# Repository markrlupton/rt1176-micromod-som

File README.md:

# RT1176 MicroMod SOM

An NXP i.MX RT1176 (Cortex-M7 1 GHz + Cortex-M4 400 MHz) on a MicroMod processor card (M.2 2222 Key E). It uses the SparkFun MicroMod Teensy pinout, so it drops into the RaceLink intercom carrier in place of the MicroMod Teensy.

- **Status:** stage 4 done: fab files in `fab/`, ordering notes in `docs/FAB_NOTES.md`, hand-build guide in `docs/HAND_BUILD.md`.
- **Schematic:** [docs/schematic.pdf](docs/schematic.pdf). Generated by `tools/schgen.py`; regenerate rather than editing in KiCad.
- **Design decisions and open items:** [docs/DESIGN.md](docs/DESIGN.md)
- **Pin map:** [docs/PINOUT.md](docs/PINOUT.md). Generated from `tools/pinmap.py`; don't edit by hand.
- **Floorplan:** [docs/floorplan_v1.png](docs/floorplan_v1.png)

## Tools

KiCad 7 + Python, the same toolchain as the intercom carrier.

| Script | Does |
|---|---|
| `tools/pinmap.py` | Single source of truth: MicroMod pin -> RT1176 pad and function |
| `tools/verify.py` | Checks the pin map against NXP's pin-mux data (Zephyr hal_nxp) and the RT1176 ball map: function exists on the pad, no pad used twice, every Teensy pin covered |
| `tools/mktable.py` | Regenerates docs/PINOUT.md |
| `tools/optimize_pins.py` | Picks RT1176 pads for each MicroMod signal to keep ball-to-finger routes short |
| `tools/floorplan.py` | Regenerates the floorplan drawing |
| `tools/libgen.py` | Builds `lib/`: RT1176 symbol (6 units, from the ball map), MicroMod card symbol and edge-finger footprint |
| `tools/schgen.py` | Builds the KiCad 7 schematic (root + 4 sheets) from one parts/nets table |
| `tools/schcheck.py` | Exports the netlist with kicad-cli and checks it against the design table, the pin map and NXP's rail rules |

Regenerate everything: `python3 tools/libgen.py && python3 tools/schgen.py && python3 tools/schcheck.py`

## Fabrication (stage 4)

`python3 tools/fab.py` writes `fab/`: Gerbers and drill (`fab/rt1176-micromod-som-gerbers.zip`), JLC BOM and
placement files, assembly drawings, a hand-build stencil, and the DRC report. Order settings: `docs/FAB_NOTES.md`.
Hand assembly: `docs/HAND_BUILD.md`.

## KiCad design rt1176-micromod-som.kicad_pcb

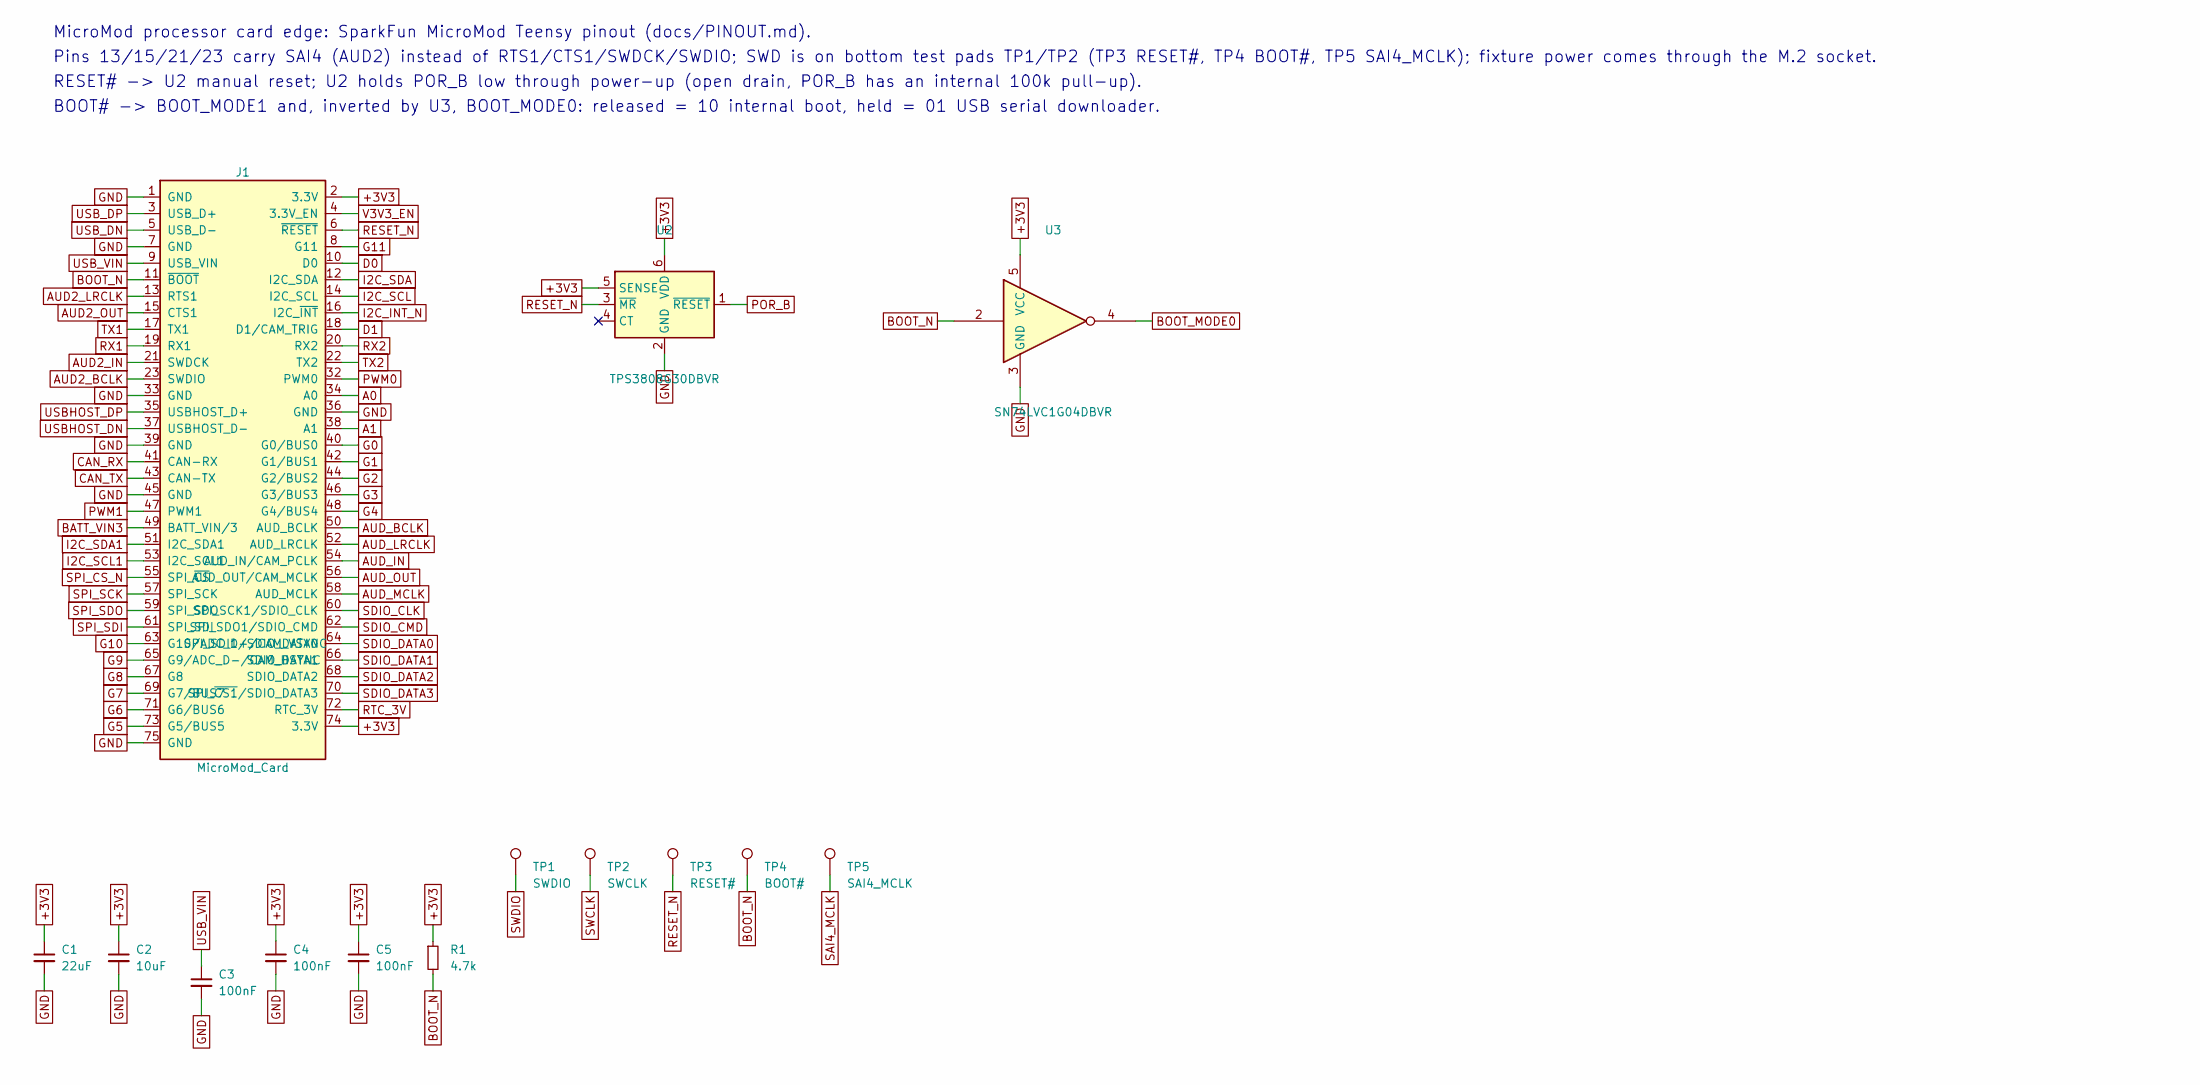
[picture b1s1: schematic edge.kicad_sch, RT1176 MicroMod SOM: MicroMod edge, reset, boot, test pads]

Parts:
C1: 22uF; C_0805_2012Metric
C2: 10uF; C_0805_2012Metric
C3, C4, C5: 100nF; C_0603_1608Metric
J1: MicroMod_Card; MicroMod_Card_Edge
R1: 4.7k; R_0603_1608Metric
TP1: SWDIO; TestPoint_Pad_D1.0mm
TP2: SWCLK; TestPoint_Pad_D1.0mm
TP3: RESET#; TestPoint_Pad_D1.0mm
TP4: BOOT#; TestPoint_Pad_D1.0mm
TP5: SAI4_MCLK; TestPoint_Pad_D1.0mm
U2: TPS3808G30DBVR; SOT-23-6; MPN TPS3808G30DBVR; LCSC C189211
U3: SN74LVC1G04DBVR; SOT-23-5; MPN SN74LVC1G04DBVR; LCSC C7827

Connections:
+3V3: C1.1, C2.1, C4.1, C5.1, J1.2 (3.3V), J1.74 (3.3V), R1.1, U2.5 (SENSE), U2.6 (VDD), U3.5 (VCC); also elsewhere on the board
A0: J1.34 (A0); also elsewhere on the board
A1: J1.38 (A1); also elsewhere on the board
AUD2_BCLK: J1.23 (SWDIO); also elsewhere on the board
AUD2_IN: J1.21 (SWDCK); also elsewhere on the board
AUD2_LRCLK: J1.13 (RTS1); also elsewhere on the board
AUD2_OUT: J1.15 (CTS1); also elsewhere on the board
AUD_BCLK: J1.50 (AUD_BCLK); also elsewhere on the board
AUD_IN: J1.54 (AUD_IN/CAM_PCLK); also elsewhere on the board
AUD_LRCLK: J1.52 (AUD_LRCLK); also elsewhere on the board
AUD_MCLK: J1.58 (AUD_MCLK); also elsewhere on the board
AUD_OUT: J1.56 (AUD_OUT/CAM_MCLK); also elsewhere on the board
BATT_VIN3: J1.49 (BATT_VIN/3); also elsewhere on the board
BOOT_MODE0: U3.4; also elsewhere on the board
BOOT_N: J1.11 (~BOOT), R1.2, TP4.1, U3.2; also elsewhere on the board
CAN_RX: J1.41 (CAN-RX); also elsewhere on the board
CAN_TX: J1.43 (CAN-TX); also elsewhere on the board
D0: J1.10 (D0); also elsewhere on the board
D1: J1.18 (D1/CAM_TRIG); also elsewhere on the board
G0: J1.40 (G0/BUS0); also elsewhere on the board
G1: J1.42 (G1/BUS1); also elsewhere on the board
G2: J1.44 (G2/BUS2); also elsewhere on the board
G3: J1.46 (G3/BUS3); also elsewhere on the board
G4: J1.48 (G4/BUS4); also elsewhere on the board
G5: J1.73 (G5/BUS5); also elsewhere on the board
G6: J1.71 (G6/BUS6); also elsewhere on the board
G7: J1.69 (G7/BUS7); also elsewhere on the board
G8: J1.67 (G8); also elsewhere on the board
G9: J1.65 (G9/ADC_D-/CAM_HSYNC); also elsewhere on the board
G10: J1.63 (G10/ADC_D+/CAM_VSYNC); also elsewhere on the board
G11: J1.8 (G11); also elsewhere on the board
GND: C1.2, C2.2, C3.2, C4.2, C5.2, J1.1 (GND), J1.7 (GND), J1.33 (GND), J1.36 (GND), J1.39 (GND), J1.45 (GND), J1.75 (GND), U2.2 (GND), U3.3 (GND); also elsewhere on the board
I2C_INT_N: J1.16 (I2C_~INT); also elsewhere on the board
I2C_SCL: J1.14 (I2C_SCL); also elsewhere on the board
I2C_SCL1: J1.53 (I2C_SCL1); also elsewhere on the board
I2C_SDA: J1.12 (I2C_SDA); also elsewhere on the board
I2C_SDA1: J1.51 (I2C_SDA1); also elsewhere on the board
POR_B: U2.1 (~RESET); also elsewhere on the board
PWM0: J1.32 (PWM0); also elsewhere on the board
PWM1: J1.47 (PWM1); also elsewhere on the board
RESET_N: J1.6 (~RESET), TP3.1, U2.3 (~MR)
RTC_3V: J1.72 (RTC_3V); also elsewhere on the board
RX1: J1.19 (RX1); also elsewhere on the board
RX2: J1.20 (RX2); also elsewhere on the board
SAI4_MCLK: TP5.1; also elsewhere on the board
SDIO_CLK: J1.60 (SPI_SCK1/SDIO_CLK); also elsewhere on the board
SDIO_CMD: J1.62 (SPI_SDO1/SDIO_CMD); also elsewhere on the board
SDIO_DATA0: J1.64 (SPI_SDI1/SDIO_DATA0); also elsewhere on the board
SDIO_DATA1: J1.66 (SDIO_DATA1); also elsewhere on the board
SDIO_DATA2: J1.68 (SDIO_DATA2); also elsewhere on the board
SDIO_DATA3: J1.70 (SPI_~CS1/SDIO_DATA3); also elsewhere on the board
SPI_CS_N: J1.55 (SPI_~CS); also elsewhere on the board
SPI_SCK: J1.57 (SPI_SCK); also elsewhere on the board
SPI_SDI: J1.61 (SPI_SDI); also elsewhere on the board
SPI_SDO: J1.59 (SPI_SDO); also elsewhere on the board
SWCLK: TP2.1; also elsewhere on the board
SWDIO: TP1.1; also elsewhere on the board
TX1: J1.17 (TX1); also elsewhere on the board
TX2: J1.22 (TX2); also elsewhere on the board
USBHOST_DN: J1.37 (USBHOST_D-); also elsewhere on the board
USBHOST_DP: J1.35 (USBHOST_D+); also elsewhere on the board
USB_DN: J1.5 (USB_D-); also elsewhere on the board
USB_DP: J1.3 (USB_D+); also elsewhere on the board
USB_VIN: C3.1, J1.9 (USB_VIN); also elsewhere on the board
V3V3_EN: J1.4 (3.3V_EN); also elsewhere on the board

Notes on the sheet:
MicroMod processor card edge: SparkFun MicroMod Teensy pinout (docs/PINOUT.md).
Pins 13/15/21/23 carry SAI4 (AUD2) instead of RTS1/CTS1/SWDCK/SWDIO; SWD is on bottom test pads TP1/TP2 (TP3 RESET#, TP4 BOOT#, TP5 SAI4_MCLK); fixture power comes through the M.2 socket.
RESET# -> U2 manual reset; U2 holds POR_B low through power-up (open drain, POR_B has an internal 100k pull-up).
BOOT# -> BOOT_MODE1 and, inverted by U3, BOOT_MODE0: released = 10 internal boot, held = 01 USB serial downloader.

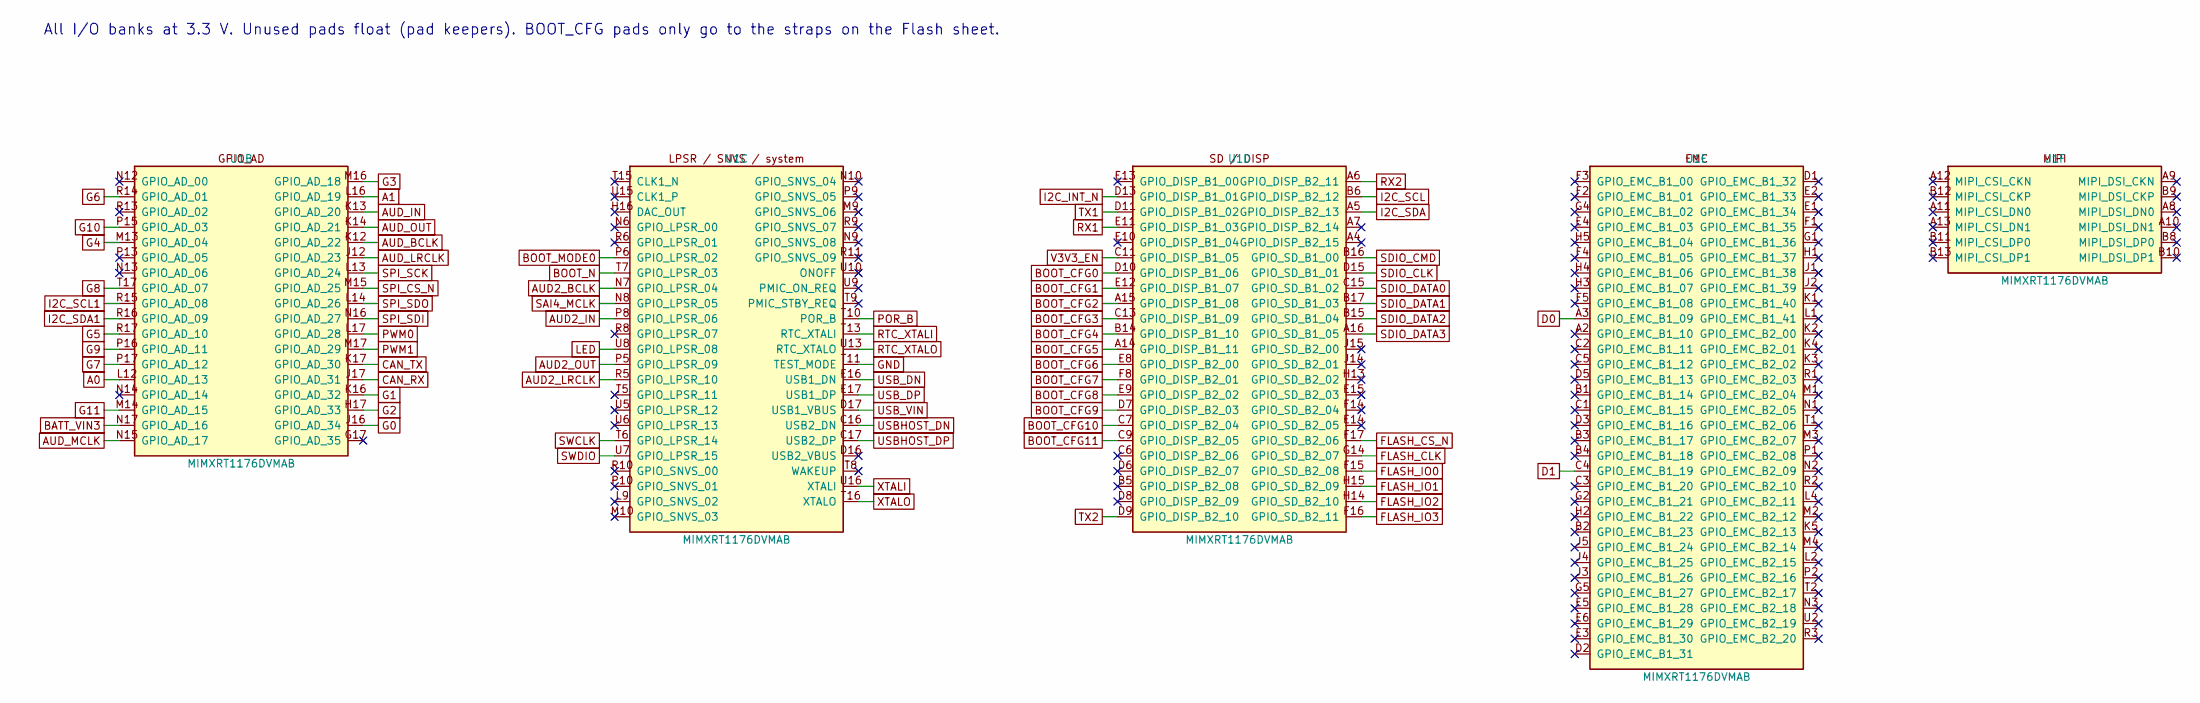
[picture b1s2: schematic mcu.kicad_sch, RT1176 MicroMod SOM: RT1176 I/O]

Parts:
U1: MIMXRT1176DVMAB; MAPBGA_14x14mm_Layout17x17_P0.8mm; MPN MIMXRT1176DVMAB

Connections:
A0: U1.L12 (GPIO_AD_13); also elsewhere on the board
A1: U1.L16 (GPIO_AD_19); also elsewhere on the board
AUD2_BCLK: U1.N7 (GPIO_LPSR_04); also elsewhere on the board
AUD2_IN: U1.P8 (GPIO_LPSR_06); also elsewhere on the board
AUD2_LRCLK: U1.R5 (GPIO_LPSR_10); also elsewhere on the board
AUD2_OUT: U1.P5 (GPIO_LPSR_09); also elsewhere on the board
AUD_BCLK: U1.K12 (GPIO_AD_22); also elsewhere on the board
AUD_IN: U1.K13 (GPIO_AD_20); also elsewhere on the board
AUD_LRCLK: U1.J12 (GPIO_AD_23); also elsewhere on the board
AUD_MCLK: U1.N15 (GPIO_AD_17); also elsewhere on the board
AUD_OUT: U1.K14 (GPIO_AD_21); also elsewhere on the board
BATT_VIN3: U1.N17 (GPIO_AD_16); also elsewhere on the board
BOOT_CFG0: U1.D10 (GPIO_DISP_B1_06); also elsewhere on the board
BOOT_CFG1: U1.E12 (GPIO_DISP_B1_07); also elsewhere on the board
BOOT_CFG2: U1.A15 (GPIO_DISP_B1_08); also elsewhere on the board
BOOT_CFG3: U1.C13 (GPIO_DISP_B1_09); also elsewhere on the board
BOOT_CFG4: U1.B14 (GPIO_DISP_B1_10); also elsewhere on the board
BOOT_CFG5: U1.A14 (GPIO_DISP_B1_11); also elsewhere on the board
BOOT_CFG6: U1.E8 (GPIO_DISP_B2_00); also elsewhere on the board
BOOT_CFG7: U1.F8 (GPIO_DISP_B2_01); also elsewhere on the board
BOOT_CFG8: U1.E9 (GPIO_DISP_B2_02); also elsewhere on the board
BOOT_CFG9: U1.D7 (GPIO_DISP_B2_03); also elsewhere on the board
BOOT_CFG10: U1.C7 (GPIO_DISP_B2_04); also elsewhere on the board
BOOT_CFG11: U1.C9 (GPIO_DISP_B2_05); also elsewhere on the board
BOOT_MODE0: U1.P6 (GPIO_LPSR_02); also elsewhere on the board
BOOT_N: U1.T7 (GPIO_LPSR_03); also elsewhere on the board
CAN_RX: U1.J17 (GPIO_AD_31); also elsewhere on the board
CAN_TX: U1.K17 (GPIO_AD_30); also elsewhere on the board
D0: U1.A3 (GPIO_EMC_B1_09); also elsewhere on the board
D1: U1.C4 (GPIO_EMC_B1_19); also elsewhere on the board
FLASH_CLK: U1.G14 (GPIO_SD_B2_07); also elsewhere on the board
FLASH_CS_N: U1.F17 (GPIO_SD_B2_06); also elsewhere on the board
FLASH_IO0: U1.F15 (GPIO_SD_B2_08); also elsewhere on the board
FLASH_IO1: U1.H15 (GPIO_SD_B2_09); also elsewhere on the board
FLASH_IO2: U1.H14 (GPIO_SD_B2_10); also elsewhere on the board
FLASH_IO3: U1.F16 (GPIO_SD_B2_11); also elsewhere on the board
G0: U1.J16 (GPIO_AD_34); also elsewhere on the board
G1: U1.K16 (GPIO_AD_32); also elsewhere on the board
G2: U1.H17 (GPIO_AD_33); also elsewhere on the board
G3: U1.M16 (GPIO_AD_18); also elsewhere on the board
G4: U1.M13 (GPIO_AD_04); also elsewhere on the board
G5: U1.R17 (GPIO_AD_10); also elsewhere on the board
G6: U1.R14 (GPIO_AD_01); also elsewhere on the board
G7: U1.P17 (GPIO_AD_12); also elsewhere on the board
G8: U1.T17 (GPIO_AD_07); also elsewhere on the board
G9: U1.P16 (GPIO_AD_11); also elsewhere on the board
G10: U1.P15 (GPIO_AD_03); also elsewhere on the board
G11: U1.M14 (GPIO_AD_15); also elsewhere on the board
GND: U1.T11 (TEST_MODE); also elsewhere on the board
I2C_INT_N: U1.D13 (GPIO_DISP_B1_01); also elsewhere on the board
I2C_SCL: U1.B6 (GPIO_DISP_B2_12); also elsewhere on the board
I2C_SCL1: U1.R15 (GPIO_AD_08); also elsewhere on the board
I2C_SDA: U1.A5 (GPIO_DISP_B2_13); also elsewhere on the board
I2C_SDA1: U1.R16 (GPIO_AD_09); also elsewhere on the board
LED: U1.U8 (GPIO_LPSR_08); also elsewhere on the board
POR_B: U1.T10 (POR_B); also elsewhere on the board
PWM0: U1.L17 (GPIO_AD_28); also elsewhere on the board
PWM1: U1.M17 (GPIO_AD_29); also elsewhere on the board
RTC_XTALI: U1.T13 (RTC_XTALI); also elsewhere on the board
RTC_XTALO: U1.U13 (RTC_XTALO); also elsewhere on the board
RX1: U1.E11 (GPIO_DISP_B1_03); also elsewhere on the board
RX2: U1.A6 (GPIO_DISP_B2_11); also elsewhere on the board
SAI4_MCLK: U1.N8 (GPIO_LPSR_05); also elsewhere on the board
SDIO_CLK: U1.D15 (GPIO_SD_B1_01); also elsewhere on the board
SDIO_CMD: U1.B16 (GPIO_SD_B1_00); also elsewhere on the board
SDIO_DATA0: U1.C15 (GPIO_SD_B1_02); also elsewhere on the board
SDIO_DATA1: U1.B17 (GPIO_SD_B1_03); also elsewhere on the board
SDIO_DATA2: U1.B15 (GPIO_SD_B1_04); also elsewhere on the board
SDIO_DATA3: U1.A16 (GPIO_SD_B1_05); also elsewhere on the board
SPI_CS_N: U1.M15 (GPIO_AD_25); also elsewhere on the board
SPI_SCK: U1.L13 (GPIO_AD_24); also elsewhere on the board
SPI_SDI: U1.N16 (GPIO_AD_27); also elsewhere on the board
SPI_SDO: U1.L14 (GPIO_AD_26); also elsewhere on the board
SWCLK: U1.T6 (GPIO_LPSR_14); also elsewhere on the board
SWDIO: U1.U7 (GPIO_LPSR_15); also elsewhere on the board
TX1: U1.D11 (GPIO_DISP_B1_02); also elsewhere on the board
TX2: U1.D9 (GPIO_DISP_B2_10); also elsewhere on the board
USBHOST_DN: U1.C16 (USB2_DN); also elsewhere on the board
USBHOST_DP: U1.C17 (USB2_DP); also elsewhere on the board
USB_DN: U1.E16 (USB1_DN); also elsewhere on the board
USB_DP: U1.E17 (USB1_DP); also elsewhere on the board
USB_VIN: U1.D17 (USB1_VBUS); also elsewhere on the board
V3V3_EN: U1.C11 (GPIO_DISP_B1_05); also elsewhere on the board
XTALI: U1.U16 (XTALI); also elsewhere on the board
XTALO: U1.T16 (XTALO); also elsewhere on the board

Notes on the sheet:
All I/O banks at 3.3 V. Unused pads float (pad keepers). BOOT_CFG pads only go to the straps on the Flash sheet.

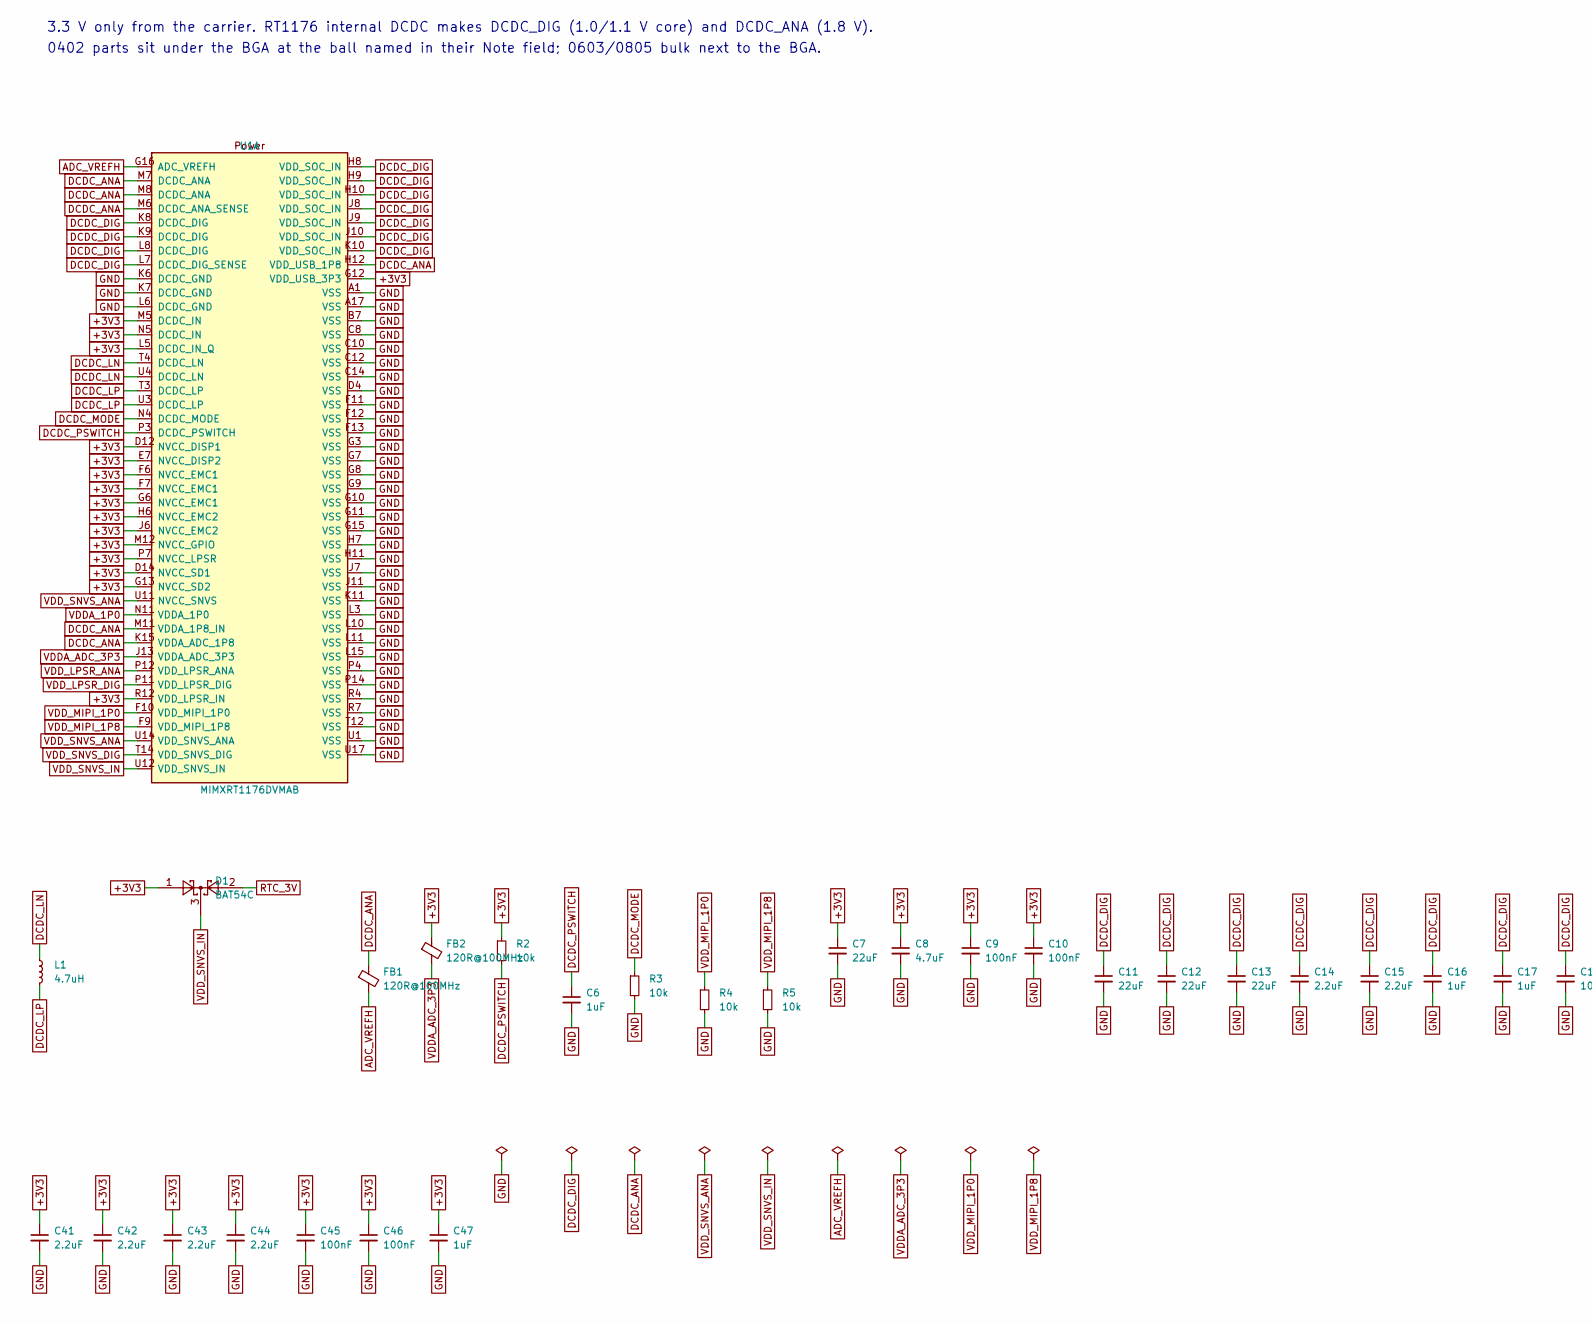
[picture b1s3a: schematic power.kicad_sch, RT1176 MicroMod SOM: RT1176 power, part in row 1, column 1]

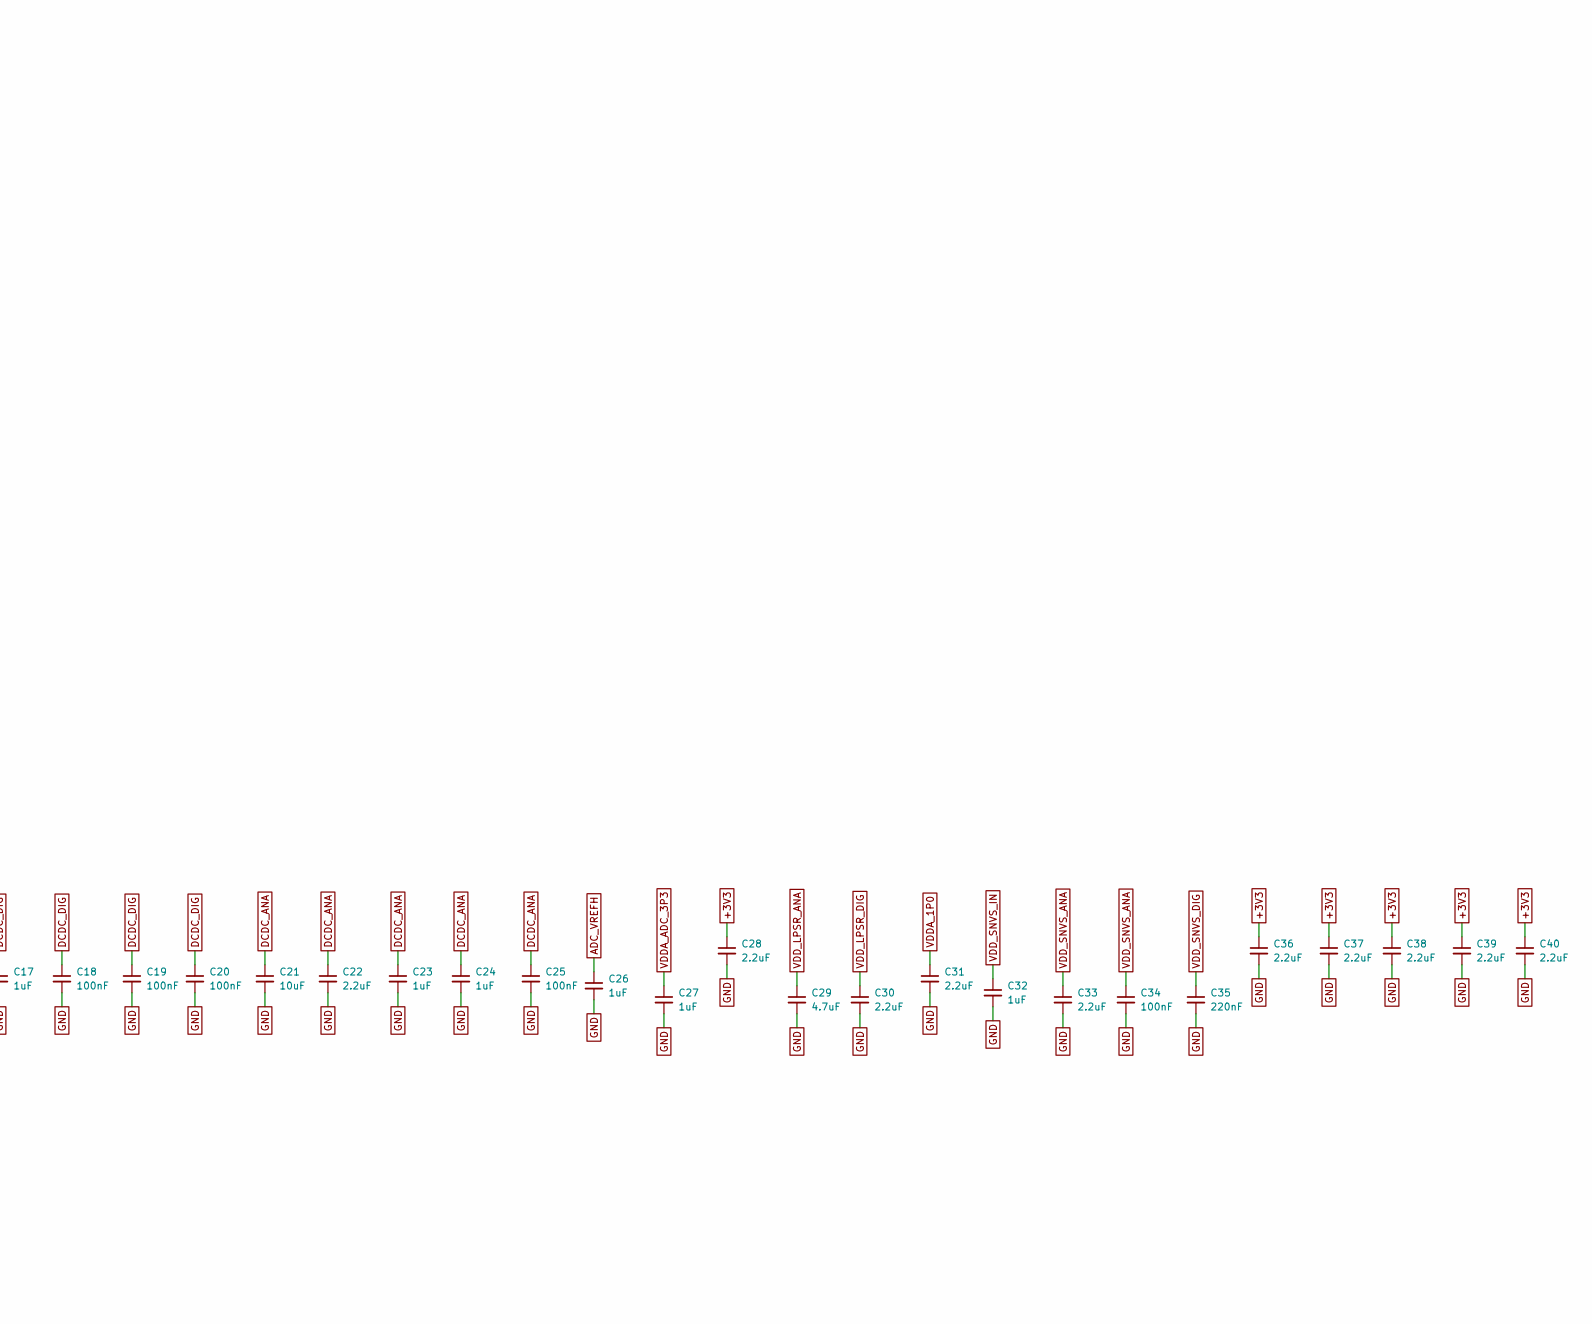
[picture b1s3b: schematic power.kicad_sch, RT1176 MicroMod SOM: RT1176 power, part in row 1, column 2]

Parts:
C6, C16, C17, C23, C24, C26, C27, C32, C47: 1uF; C_0402_1005Metric
C7, C11, C12, C13: 22uF; C_0805_2012Metric
C8: 4.7uF; C_0603_1608Metric
C9, C10, C18, C19, C20, C25, C34, C45, C46: 100nF; C_0402_1005Metric
C14, C15, C22, C28, C30, C31, C33, C36, C37, C38, C39, C40, C41, C42, C43, C44: 2.2uF; C_0402_1005Metric
C21: 10uF; C_0603_1608Metric
C29: 4.7uF; C_0402_1005Metric
C35: 220nF; C_0402_1005Metric
D1: BAT54C; SOT-23; MPN BAT54C,215; LCSC C37704
FB1, FB2: 120R@100MHz; L_0603_1608Metric
L1: 4.7uH; L_Changjiang_FNR4030S; MPN SWPA4030S4R7MT; LCSC C57269
R2, R3, R4, R5: 10k; R_0402_1005Metric
U1: MIMXRT1176DVMAB; MAPBGA_14x14mm_Layout17x17_P0.8mm; MPN MIMXRT1176DVMAB

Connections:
+3V3: C7.1, C8.1, C9.1, C10.1, C28.1, C36.1, C37.1, C38.1, C39.1, C40.1, C41.1, C42.1, C43.1, C44.1, C45.1, C46.1, C47.1, D1.1, FB2.1, R2.1, U1.D12 (NVCC_DISP1), U1.D14 (NVCC_SD1), U1.E7 (NVCC_DISP2), U1.F6 (NVCC_EMC1), U1.F7 (NVCC_EMC1), U1.G6 (NVCC_EMC1), U1.G12 (VDD_USB_3P3), U1.G13 (NVCC_SD2), U1.H6 (NVCC_EMC2), U1.J6 (NVCC_EMC2), U1.L5 (DCDC_IN_Q), U1.M5 (DCDC_IN), U1.M12 (NVCC_GPIO), U1.N5 (DCDC_IN), U1.P7 (NVCC_LPSR), U1.R12 (VDD_LPSR_IN); also elsewhere on the board
ADC_VREFH: C26.1, FB1.2, U1.G16 (ADC_VREFH)
DCDC_ANA: C21.1, C22.1, C23.1, C24.1, C25.1, FB1.1, U1.H12 (VDD_USB_1P8), U1.K15 (VDDA_ADC_1P8), U1.M6 (DCDC_ANA_SENSE), U1.M7 (DCDC_ANA), U1.M8 (DCDC_ANA), U1.M11 (VDDA_1P8_IN)
DCDC_DIG: C11.1, C12.1, C13.1, C14.1, C15.1, C16.1, C17.1, C18.1, C19.1, C20.1, U1.H8 (VDD_SOC_IN), U1.H9 (VDD_SOC_IN), U1.H10 (VDD_SOC_IN), U1.J8 (VDD_SOC_IN), U1.J9 (VDD_SOC_IN), U1.J10 (VDD_SOC_IN), U1.K8 (DCDC_DIG), U1.K9 (DCDC_DIG), U1.K10 (VDD_SOC_IN), U1.L7 (DCDC_DIG_SENSE), U1.L8 (DCDC_DIG)
DCDC_LN: L1.1, U1.T4 (DCDC_LN), U1.U4 (DCDC_LN)
DCDC_LP: L1.2, U1.T3 (DCDC_LP), U1.U3 (DCDC_LP)
DCDC_MODE: R3.1, U1.N4 (DCDC_MODE)
DCDC_PSWITCH: C6.1, R2.2, U1.P3 (DCDC_PSWITCH)
GND: C6.2, C7.2, C8.2, C9.2, C10.2, C11.2, C12.2, C13.2, C14.2, C15.2, C16.2, C17.2, C18.2, C19.2, C20.2, C21.2, C22.2, C23.2, C24.2, C25.2, C26.2, C27.2, C28.2, C29.2, C30.2, C31.2, C32.2, C33.2, C34.2, C35.2, C36.2, C37.2, C38.2, C39.2, C40.2, C41.2, C42.2, C43.2, C44.2, C45.2, C46.2, C47.2, R3.2, R4.2, R5.2, U1.A1 (VSS), U1.A17 (VSS), U1.B7 (VSS), U1.C8 (VSS), U1.C10 (VSS), U1.C12 (VSS), U1.C14 (VSS), U1.D4 (VSS), U1.F11 (VSS), U1.F12 (VSS), U1.F13 (VSS), U1.G3 (VSS), U1.G7 (VSS), U1.G8 (VSS), U1.G9 (VSS), U1.G10 (VSS), U1.G11 (VSS), U1.G15 (VSS), U1.H7 (VSS), U1.H11 (VSS), U1.J7 (VSS), U1.J11 (VSS), U1.K6 (DCDC_GND), U1.K7 (DCDC_GND), U1.K11 (VSS), U1.L3 (VSS), U1.L6 (DCDC_GND), U1.L10 (VSS), U1.L11 (VSS), U1.L15 (VSS), U1.P4 (VSS), U1.P14 (VSS), U1.R4 (VSS), U1.R7 (VSS), U1.T12 (VSS), U1.U1 (VSS), U1.U17 (VSS); also elsewhere on the board
RTC_3V: D1.2; also elsewhere on the board
VDDA_1P0: C31.1, U1.N11 (VDDA_1P0)
VDDA_ADC_3P3: C27.1, FB2.2, U1.J13 (VDDA_ADC_3P3)
VDD_LPSR_ANA: C29.1, U1.P12 (VDD_LPSR_ANA)
VDD_LPSR_DIG: C30.1, U1.P11 (VDD_LPSR_DIG)
VDD_MIPI_1P0: R4.1, U1.F10 (VDD_MIPI_1P0)
VDD_MIPI_1P8: R5.1, U1.F9 (VDD_MIPI_1P8)
VDD_SNVS_ANA: C33.1, C34.1, U1.U11 (NVCC_SNVS), U1.U14 (VDD_SNVS_ANA)
VDD_SNVS_DIG: C35.1, U1.T14 (VDD_SNVS_DIG)
VDD_SNVS_IN: C32.1, D1.3, U1.U12 (VDD_SNVS_IN)

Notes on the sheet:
3.3 V only from the carrier. RT1176 internal DCDC makes DCDC_DIG (1.0/1.1 V core) and DCDC_ANA (1.8 V).
0402 parts sit under the BGA at the ball named in their Note field; 0603/0805 bulk next to the BGA.

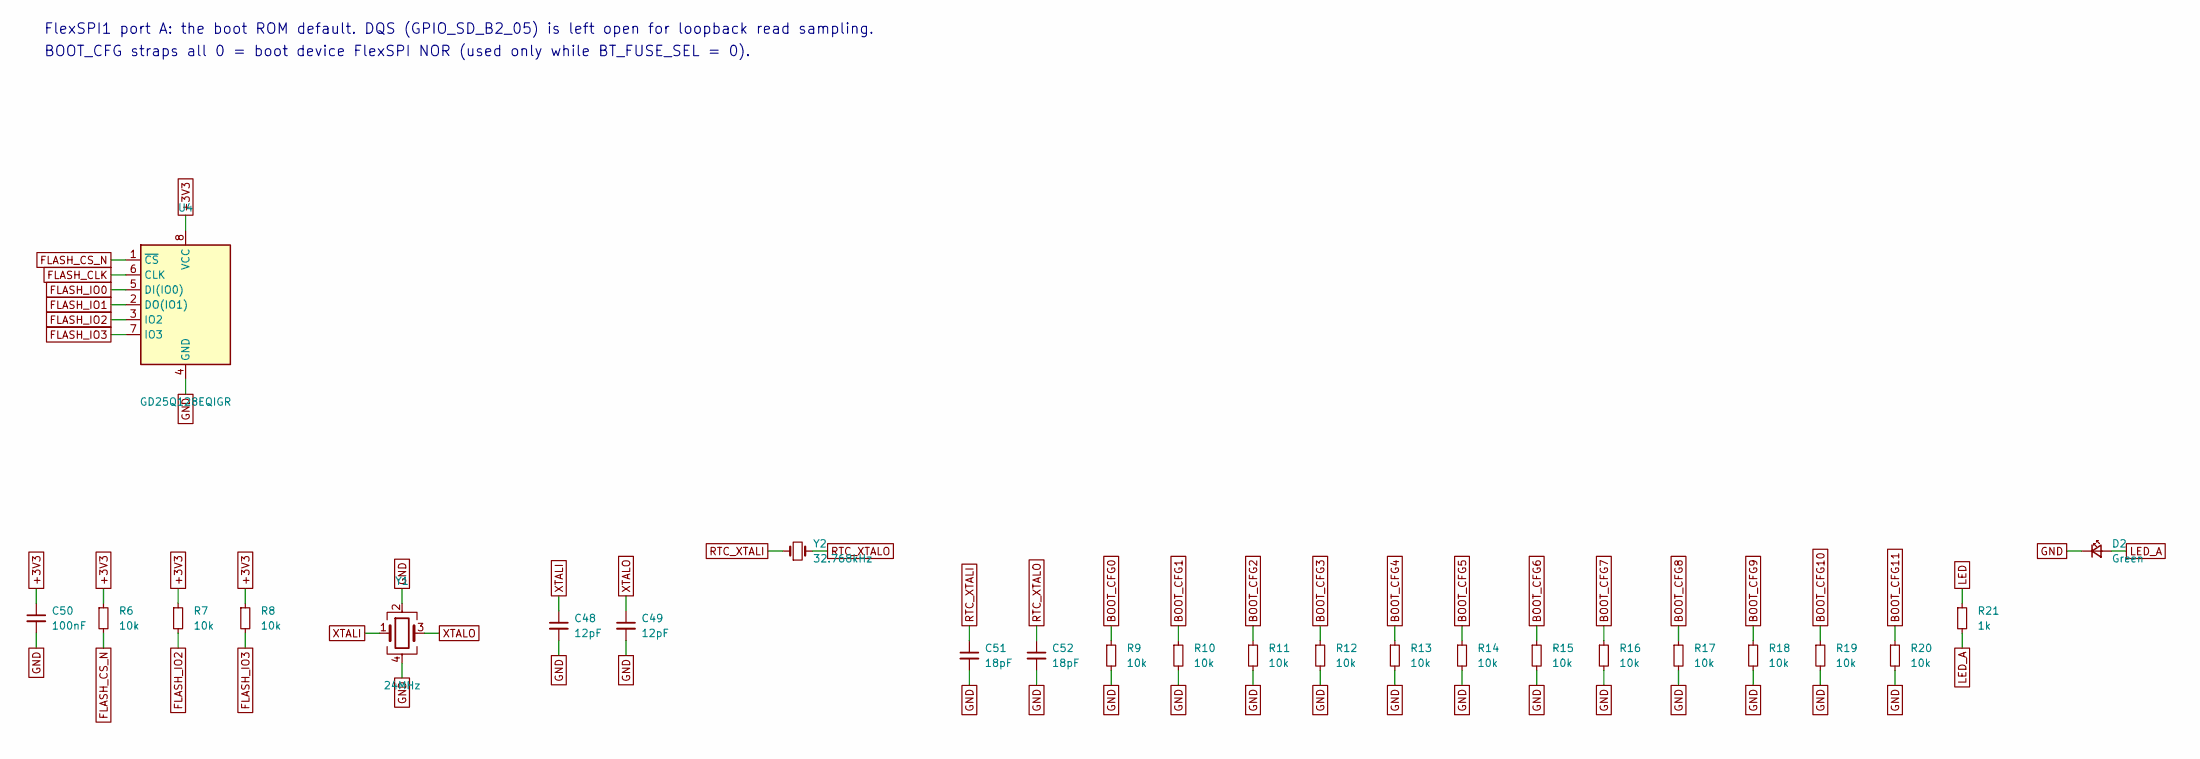
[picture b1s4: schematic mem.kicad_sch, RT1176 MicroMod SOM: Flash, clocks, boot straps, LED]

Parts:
C48, C49: 12pF; C_0402_1005Metric
C50: 100nF; C_0603_1608Metric
C51, C52: 18pF; C_0402_1005Metric
D2: Green; LED_0603_1608Metric
R6, R7, R8: 10k; R_0603_1608Metric
R9, R10, R11, R12, R13, R14, R15, R16, R17, R18, R19, R20: 10k; R_0402_1005Metric
R21: 1k; R_0603_1608Metric
U4: GD25Q128EQIGR; USON-8-1EP_4x4mm_P0.8mm_EP2.3x3mm_GigaDevice; MPN GD25Q128EQIGR
Y1: 24MHz; Crystal_SMD_2016-4Pin_2.0x1.6mm
Y2: 32.768kHz; Crystal_SMD_3215-2Pin_3.2x1.5mm; MPN Q13FC1350000400; LCSC C32346

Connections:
+3V3: C50.1, R6.1, R7.1, R8.1, U4.8 (VCC); also elsewhere on the board
BOOT_CFG0: R9.1; also elsewhere on the board
BOOT_CFG1: R10.1; also elsewhere on the board
BOOT_CFG2: R11.1; also elsewhere on the board
BOOT_CFG3: R12.1; also elsewhere on the board
BOOT_CFG4: R13.1; also elsewhere on the board
BOOT_CFG5: R14.1; also elsewhere on the board
BOOT_CFG6: R15.1; also elsewhere on the board
BOOT_CFG7: R16.1; also elsewhere on the board
BOOT_CFG8: R17.1; also elsewhere on the board
BOOT_CFG9: R18.1; also elsewhere on the board
BOOT_CFG10: R19.1; also elsewhere on the board
BOOT_CFG11: R20.1; also elsewhere on the board
FLASH_CLK: U4.6 (CLK); also elsewhere on the board
FLASH_CS_N: R6.2, U4.1 (~CS); also elsewhere on the board
FLASH_IO0: U4.5 (DI(IO0)); also elsewhere on the board
FLASH_IO1: U4.2 (DO(IO1)); also elsewhere on the board
FLASH_IO2: R7.2, U4.3 (IO2); also elsewhere on the board
FLASH_IO3: R8.2, U4.7 (IO3); also elsewhere on the board
GND: C48.2, C49.2, C50.2, C51.2, C52.2, D2.1 (K), R9.2, R10.2, R11.2, R12.2, R13.2, R14.2, R15.2, R16.2, R17.2, R18.2, R19.2, R20.2, U4.4 (GND), Y1.2, Y1.4; also elsewhere on the board
LED: R21.1; also elsewhere on the board
LED_A: D2.2 (A), R21.2
RTC_XTALI: C51.1, Y2.1; also elsewhere on the board
RTC_XTALO: C52.1, Y2.2; also elsewhere on the board
XTALI: C48.1, Y1.1; also elsewhere on the board
XTALO: C49.1, Y1.3; also elsewhere on the board

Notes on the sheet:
FlexSPI1 port A: the boot ROM default. DQS (GPIO_SD_B2_05) is left open for loopback read sampling.
BOOT_CFG straps all 0 = boot device FlexSPI NOR (used only while BT_FUSE_SEL = 0).

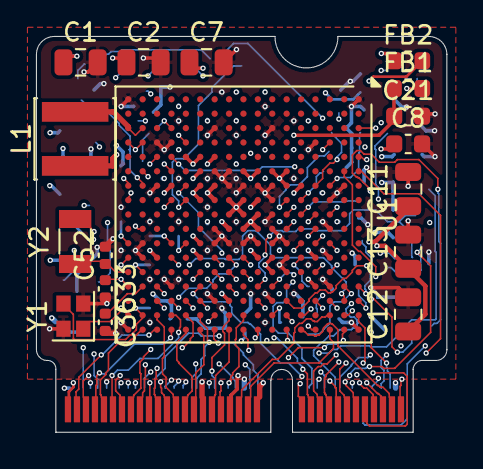
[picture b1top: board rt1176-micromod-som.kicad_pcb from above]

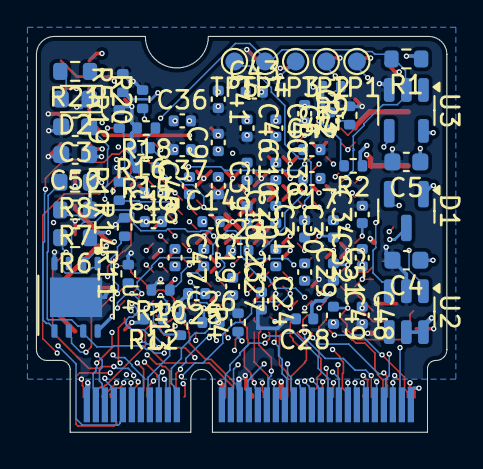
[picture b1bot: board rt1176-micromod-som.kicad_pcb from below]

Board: 6 copper layers, 22.8 x 22.0 mm, 90 parts (72 on the bottom side), 105 nets.

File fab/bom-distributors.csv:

Line,Qty per board,Qty for 5 boards,Manufacturer,Manufacturer Part Number,Description,Designators,Footprint,Side
1,5,35,Samsung,CL21A226MAQNNNE,Cap ceramic 22 uF 25 V X5R 0805,C1 C7 C11 C12 C13,C_0805_2012Metric,top
2,1,15,Samsung,CL21A106KAYNNNE,Cap ceramic 10 uF 25 V X5R 0805,C2,C_0805_2012Metric,top
3,4,30,Yageo,CC0603KRX7R9BB104,Cap ceramic 100 nF 50 V X7R 0603,C3 C4 C5 C50,C_0603_1608Metric,bottom
4,9,55,Samsung,CL05A105KA5NQNC,Cap ceramic 1 uF 25 V X5R 0402,C6 C16 C17 C23 C24 C26 C27 C32 C47,C_0402_1005Metric,bottom
5,1,15,Samsung,CL10A475KO8NNNC,Cap ceramic 4.7 uF 16 V X5R 0603,C8,C_0603_1608Metric,top
6,9,55,Samsung,CL05B104KO5NNNC,Cap ceramic 100 nF 16 V X7R 0402,C9 C10 C18 C19 C20 C25 C34 C45 C46,C_0402_1005Metric,bottom
7,16,90,Samsung,CL05A225MQ5NSNC,Cap ceramic 2.2 uF 6.3 V X5R 0402,C14 C15 C22 C28 C30 C31 C33 C36 C37 C38 C39 C40 C41 C42 C43 C44,C_0402_1005Metric,bottom
8,1,15,Samsung,CL10A106KP8NNNC,Cap ceramic 10 uF 10 V X5R 0603,C21,C_0603_1608Metric,top
9,1,15,Samsung,CL05A475MP5NRNC,Cap ceramic 4.7 uF 10 V X5R 0402,C29,C_0402_1005Metric,bottom
10,1,15,Samsung,CL05B224KO5NNNC,Cap ceramic 220 nF 16 V X7R 0402,C35,C_0402_1005Metric,bottom
11,2,20,Murata,GRM1555C1H120JA01D,Cap ceramic 12 pF 50 V C0G 0402,C48 C49,C_0402_1005Metric,bottom
12,2,20,Murata,GRM1555C1H180JA01D,Cap ceramic 18 pF 50 V C0G 0402,C51 C52,C_0402_1005Metric,bottom/top
13,1,6,Nexperia,"BAT54C,215",Schottky dual common cathode 30 V SOT-23,D1,SOT-23,bottom
14,1,6,Lite-On,LTST-C191KGKT,LED green 0603,D2,LED_0603_1608Metric,bottom
15,2,20,Murata,BLM18PG121SN1D,Ferrite bead 120 R @ 100 MHz 2 A 0603,FB1 FB2,L_0603_1608Metric,top
16,1,6,Sunlord,SWPA4030S4R7MT,Inductor 4.7 uH 2 A shielded 4x4x3 mm,L1,L_Changjiang_FNR4030S,top
17,4,30,Yageo,RC0603FR-0710KL,Res 10 k 1% 0603,R1 R6 R7 R8,R_0603_1608Metric,bottom
18,16,90,Yageo,RC0402FR-0710KL,Res 10 k 1% 0402,R2 R3 R4 R5 R9 R10 R11 R12 R13 R14 R15 R16 R17 R18 R19 R20,R_0402_1005Metric,bottom
19,1,15,Yageo,RC0603FR-071KL,Res 1 k 1% 0603,R21,R_0603_1608Metric,bottom
20,1,6,NXP,MIMXRT1176DVMAB,"i.MX RT1176 MCU, 1 GHz M7 + 400 MHz M4, 289 MAPBGA",U1,MAPBGA_14x14mm_Layout17x17_P0.8mm,top
21,1,6,Texas Instruments,TPS3808G30DBVR,"Voltage supervisor 2.79 V, manual reset, SOT-23-6",U2,SOT-23-6,bottom
22,1,6,Texas Instruments,SN74LVC1G04DBVR,Single inverter SOT-23-5,U3,SOT-23-5,bottom
23,1,6,GigaDevice,GD25Q128EQIGR,QSPI NOR flash 128 Mbit (16 MB) USON-8 4x4,U4,USON-8-1EP_4x4mm_P0.8mm_EP2.3x3mm_GigaDevice,bottom
24,1,6,Abracon,ABM11W-24.0000MHZ-8-D1X-T3,Crystal 24 MHz 8 pF 10 ppm 2.0x1.6 mm,Y1,Crystal_SMD_2016-4Pin_2.0x1.6mm,top
25,1,6,Epson,Q13FC1350000400,Crystal 32.768 kHz 12.5 pF FC-135 3.2x1.5 mm,Y2,Crystal_SMD_3215-2Pin_3.2x1.5mm,top
